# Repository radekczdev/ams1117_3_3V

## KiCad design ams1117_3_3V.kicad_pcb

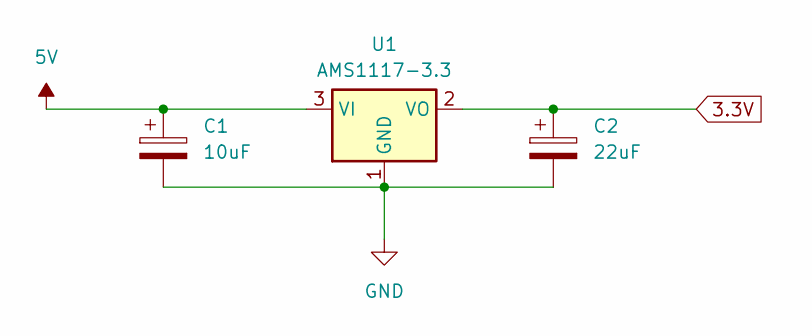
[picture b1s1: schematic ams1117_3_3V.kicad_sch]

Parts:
C1: 10uF; CP_Radial_D6.3mm_P2.50mm
C2: 22uF; CP_Radial_D5.0mm_P2.50mm
U1: AMS1117-3.3; SOT-223-3_TabPin2

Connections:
3.3V: C2.1, U1.2 (VO)
5V: C1.1, U1.3 (VI)
GND: C1.2, C2.2, U1.1 (GND)

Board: 2 copper layers, 3 parts (0 on the bottom side), 3 nets, no tracks yet.

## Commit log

2025-04-09 first commit with ams1117 files
2025-04-11 Modified schematic
